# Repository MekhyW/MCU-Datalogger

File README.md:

# MCU Datalogger

MCU datalogger with built-in 512K EEPROM and clock, made using KiCad

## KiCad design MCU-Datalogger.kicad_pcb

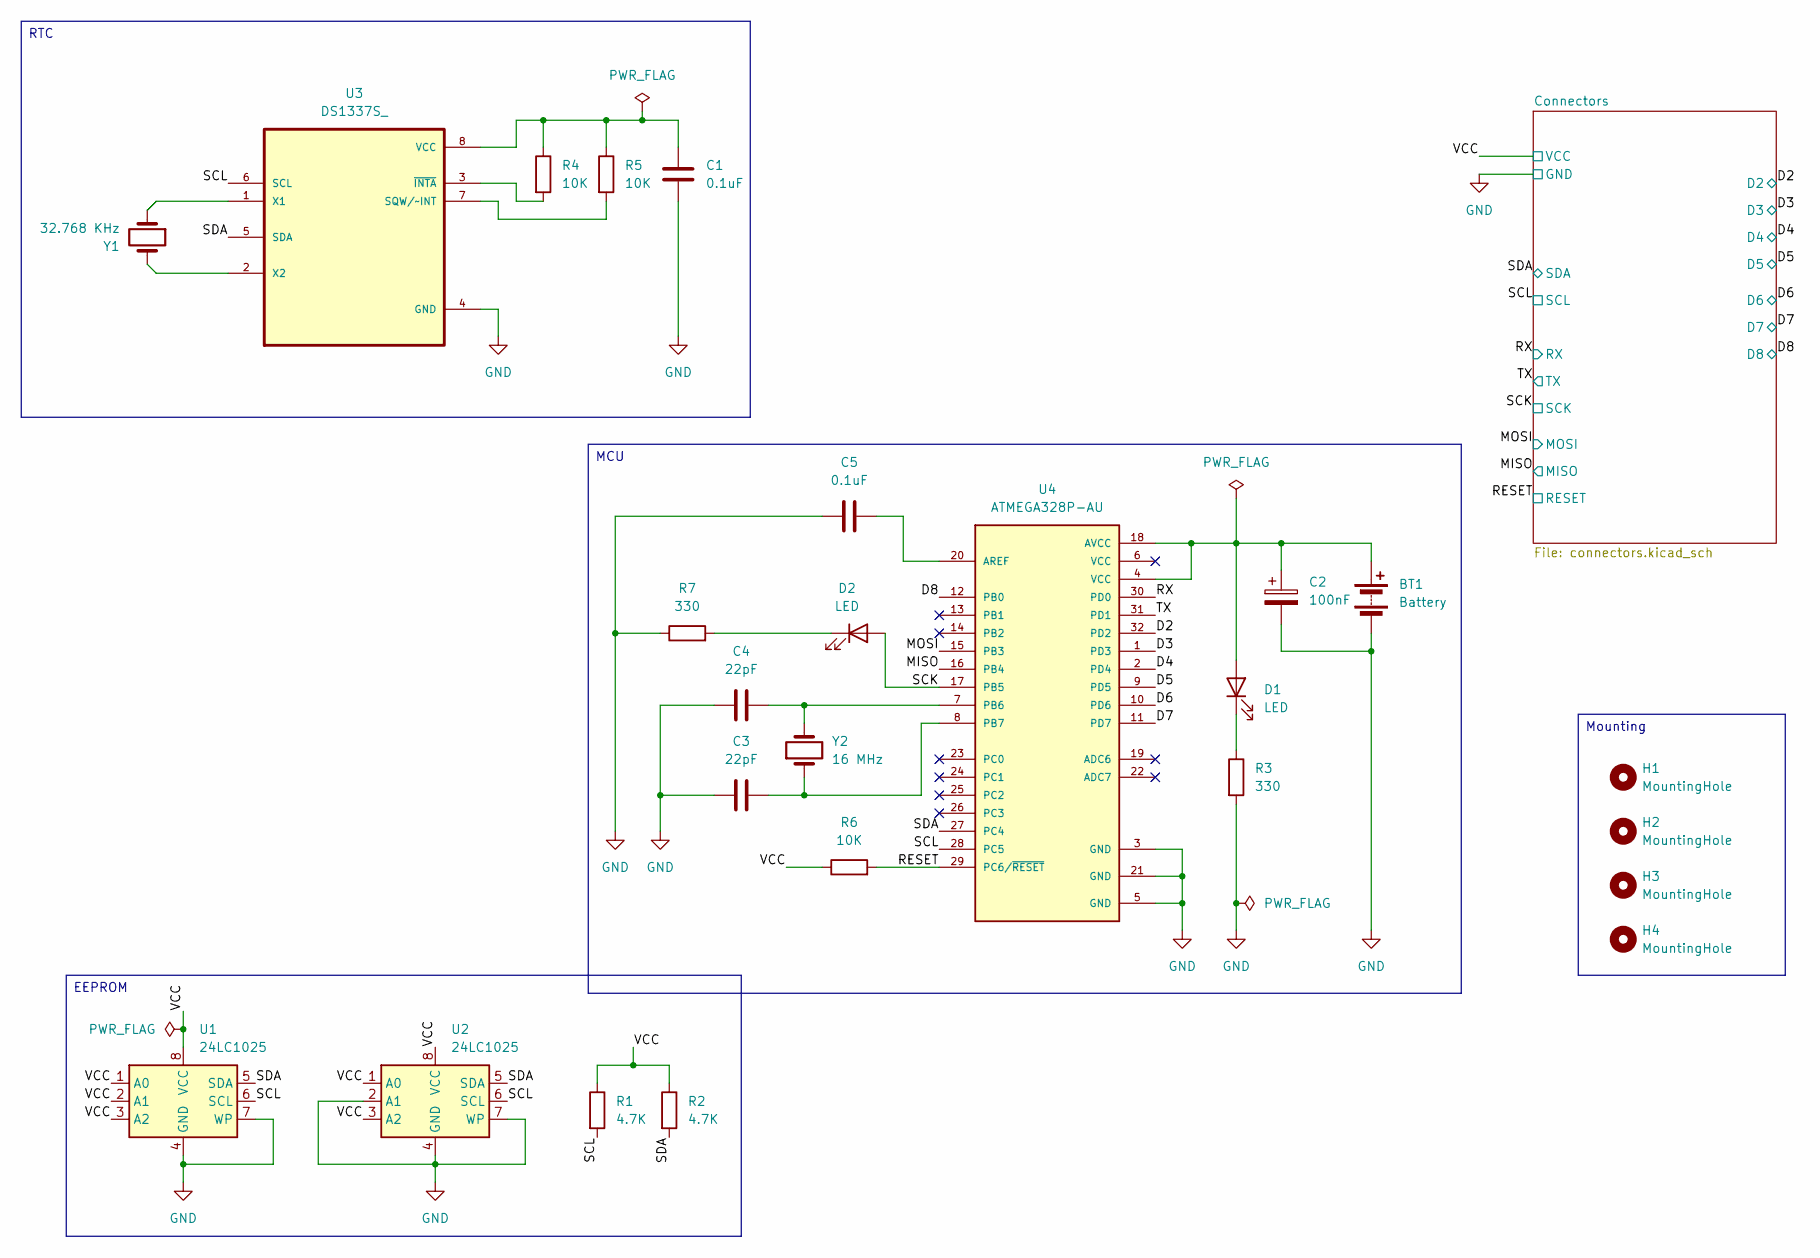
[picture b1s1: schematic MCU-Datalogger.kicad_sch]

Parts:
BT1: Battery; PinHeader_1x02_P2.54mm_Vertical
C1, C5: 0.1uF; C_0805_2012Metric
C2: 100nF; C_0805_2012Metric
C3, C4: 22pF; C_0805_2012Metric
D1, D2: LED; LED_0805_2012Metric
H1, H2, H3, H4: MountingHole; MountingHole_2.1mm
R1, R2: 4.7K; R_0805_2012Metric
R3, R7: 330; R_0805_2012Metric
R4, R5, R6: 10K; R_0805_2012Metric
U1, U2: 24LC1025; SOIC-8_3.9x4.9mm_P1.27mm
U3: DS1337S_; SOIC127P600X175-8N
U4: ATMEGA328P-AU; QFP80P900X900X120-32N; PARTREV 8271A
Y1: 32.768 KHz; Crystal_SMD_5032-2Pin_5.0x3.2mm_HandSoldering
Y2: 16 MHz; Crystal_SMD_5032-2Pin_5.0x3.2mm_HandSoldering

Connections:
/D2: U4.32 (PD2); also elsewhere on the board
/D3: U4.1 (PD3); also elsewhere on the board
/D4: U4.2 (PD4); also elsewhere on the board
/D5: U4.9 (PD5); also elsewhere on the board
/D6: U4.10 (PD6); also elsewhere on the board
/D7: U4.11 (PD7); also elsewhere on the board
/D8: U4.12 (PB0); also elsewhere on the board
/MISO: U4.16 (PB4); also elsewhere on the board
/MOSI: U4.15 (PB3); also elsewhere on the board
/RESET: R6.2, U4.29 (PC6/~RESET); also elsewhere on the board
/RX: U4.30 (PD0); also elsewhere on the board
/SCK: D2.2 (A), U4.17 (PB5); also elsewhere on the board
/SCL: R1.2, U1.6 (SCL), U2.6 (SCL), U3.6 (SCL), U4.28 (PC5); also elsewhere on the board
/SDA: R2.2, U1.5 (SDA), U2.5 (SDA), U3.5 (SDA), U4.27 (PC4); also elsewhere on the board
/TX: U4.31 (PD1); also elsewhere on the board
/VCC: R1.1, R2.1, R6.1, U1.1 (A0), U1.2 (A1), U1.3 (A2), U1.8 (VCC), U2.1 (A0), U2.3 (A2), U2.8 (VCC); also elsewhere on the board
GND: BT1.2 (-), C1.2, C2.2, C3.1, C4.1, C5.1, R3.2, R7.1, U1.4 (GND), U1.7 (WP), U2.2 (A1), U2.4 (GND), U2.7 (WP), U3.4 (GND), U4.3 (GND), U4.5 (GND), U4.21 (GND); also elsewhere on the board
unnamed: BT1.1 (+), C2.1, D1.2 (A), U4.4 (VCC), U4.18 (AVCC)
unnamed: D1.1 (K), R3.1
unnamed: D2.1 (K), R7.2
unnamed: R5.2, U3.7 (SQW/~INT)
unnamed: C1.1, R4.1, R5.1, U3.8 (VCC)
unnamed: U3.1 (X1), Y1.1
unnamed: U3.2 (X2), Y1.2
unnamed: R4.2, U3.3 (~INTA)
unnamed: C5.2, U4.20 (AREF)
unnamed: C4.2, U4.7 (PB6), Y2.2
unnamed: C3.2, U4.8 (PB7), Y2.1

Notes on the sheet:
RTC
EEPROM
Mounting
MCU

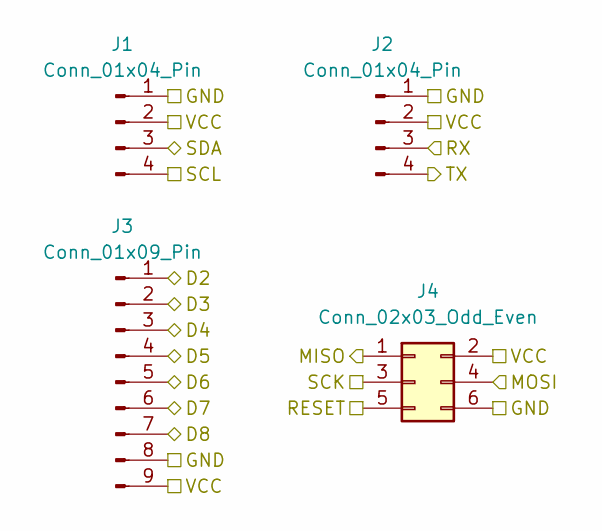
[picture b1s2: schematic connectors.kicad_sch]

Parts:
J1, J2: Conn_01x04_Pin; PinHeader_1x04_P2.54mm_Vertical
J3: Conn_01x09_Pin; PinHeader_1x09_P2.54mm_Vertical
J4: Conn_02x03_Odd_Even; PinHeader_2x03_P2.54mm_Vertical

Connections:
/D2: J3.1; also elsewhere on the board
/D3: J3.2; also elsewhere on the board
/D4: J3.3; also elsewhere on the board
/D5: J3.4; also elsewhere on the board
/D6: J3.5; also elsewhere on the board
/D7: J3.6; also elsewhere on the board
/D8: J3.7; also elsewhere on the board
/MISO: J4.1; also elsewhere on the board
/MOSI: J4.4; also elsewhere on the board
/RESET: J4.5; also elsewhere on the board
/RX: J2.3; also elsewhere on the board
/SCK: J4.3; also elsewhere on the board
/SCL: J1.4; also elsewhere on the board
/SDA: J1.3; also elsewhere on the board
/TX: J2.4; also elsewhere on the board
/VCC: J1.2, J2.2, J3.9, J4.2; also elsewhere on the board
GND: J1.1, J2.1, J3.8, J4.6; also elsewhere on the board

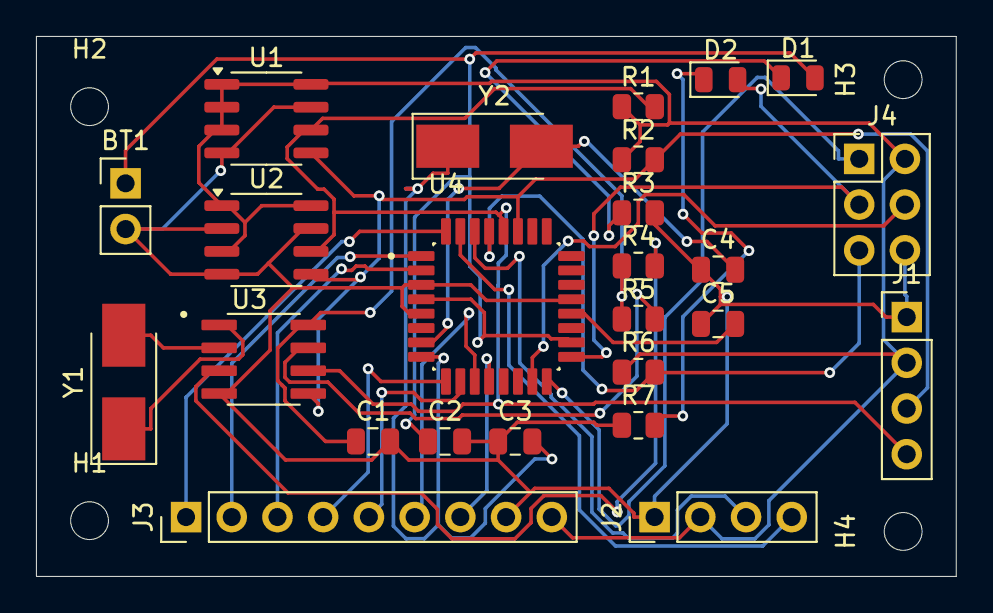
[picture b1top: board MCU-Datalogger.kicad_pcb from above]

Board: 2 copper layers, 51.1 x 30.0 mm, 29 parts (0 on the bottom side), 28 nets.

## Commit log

2025-05-02 Spawn project
2025-05-02 moved to root
2025-05-03 symbols
2025-05-03 positioning
2025-05-03 component values
2025-05-03 footprints
2025-05-03 schematic wiring
2025-05-03 comments
2025-05-03 update models
2025-05-03 render
2025-05-03 fix bugs
2025-05-03 gerber
